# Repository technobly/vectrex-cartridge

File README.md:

Vectrex Cartridge and Vectrex LED board
===

So you wanna produce a Vectrex game and you need a 32KB cartridge with high score save support? Here's your reference design! Order it as is or customize it with your own graphics.  Supports 32KB and 64KB bankswitched games.  Supports 32KB games with DS2431+ high score save.  See Schematic for configuration options.

The RGB LED is also optional, but looks great in the translucent cartridge shells.  It lights up one of 8 colors based on the Red-Green-Blue DIP switch, yes black is a color of light ;-)

What makes this Vectrex Cartridge design different from others out there?  Well, the design is originally based on Frank Buss' Vectrex cart edge connector, but it has been significantly fixed.  The soldermask has been removed from around all of the fingers, the fingers themselves are not as wide as Frank's, and the spacing of everything has been updated to match original carts as close as possible.

Yes these fit in [Sean Kelly reproduction cartridge shells](http://www.vectrexmulti.com/order2.html#!/Vectrex-Empty-Cartridge-Shells/c/38886086/offset=0&sort=normal) perfectly!

Also included here is a simple RGB LED board add-on.  Maybe you already have a PCB but you don't have the cool LED? Easy, just add this one to the bottom.  It fits perfectly under most 28 pin 32KB/64KB EPROMS.

Got a Custom PCB logo request?
===
Join the [VEXTREME Discord server](https://discord.gg/VDssGVJ) to chat with @technobly about your request

BOM and Parts ordering
===

All the parts are described in [Bill of Materials](bom/)

You can use these Digi-Key shared carts to order the parts!
[Vectrex Cartridge](https://www.digikey.com/short/z2vf9n) or
[Vectrex LED](https://www.digikey.com/short/z2vf4d)

Ordering PCB's
===

OSHPark is a good place to order with purple or the new "after dark" theme color scheme.  You can upload the KiCad `vextrex-cartridge-tall.kicad_pcb` or `vextrex-cartridge-short.kicad_pcb` there directly.  I would download this entire Github repo ZIP file first though instead of just trying to save the PCB file from your browser.  Here's a shared link for [Vectrex LED v1.0](https://oshpark.com/shared_projects/dIH6AJOJ)

Another way to order PCB's is by using the included [gerbers-tall-design](gerbers/vectrex-cartridge-tall-v1.2.zip) or [gerbers-short-design](gerbers/vectrex-cartridge-short-v1.4.zip) and uploading those with all of the necessary specs to companies like [PCBWay](https://www.pcbway.com) or [JLCPCB](https://jlcpcb.com)

## :pencil: **Don't forget to make your board finish at least ENIG (gold flash) with a 45 degree chamfered edge. [Check out my test video here on why you don't want to settle for HASL finish.](https://www.youtube.com/watch?v=6tANHqar0rI&ab_channel=PlayVectrex)**

## :boom: **[How to Build a Vectrex Game Cartridge](https://www.youtube.com/watch?v=CAzmB-9mdWY)**

Or with hard gold contacts if you really want to spend some money, and make a cart that will last forever.

LICENSE
===

CERN OHL v2.0 Permissive - essentially do whatever you want, but if you make a ton of money off of this... [buy me some coffees please!](https://buymeacoffee.com/XzUGYrhL3)  Full [LICENSE here](LICENSE)

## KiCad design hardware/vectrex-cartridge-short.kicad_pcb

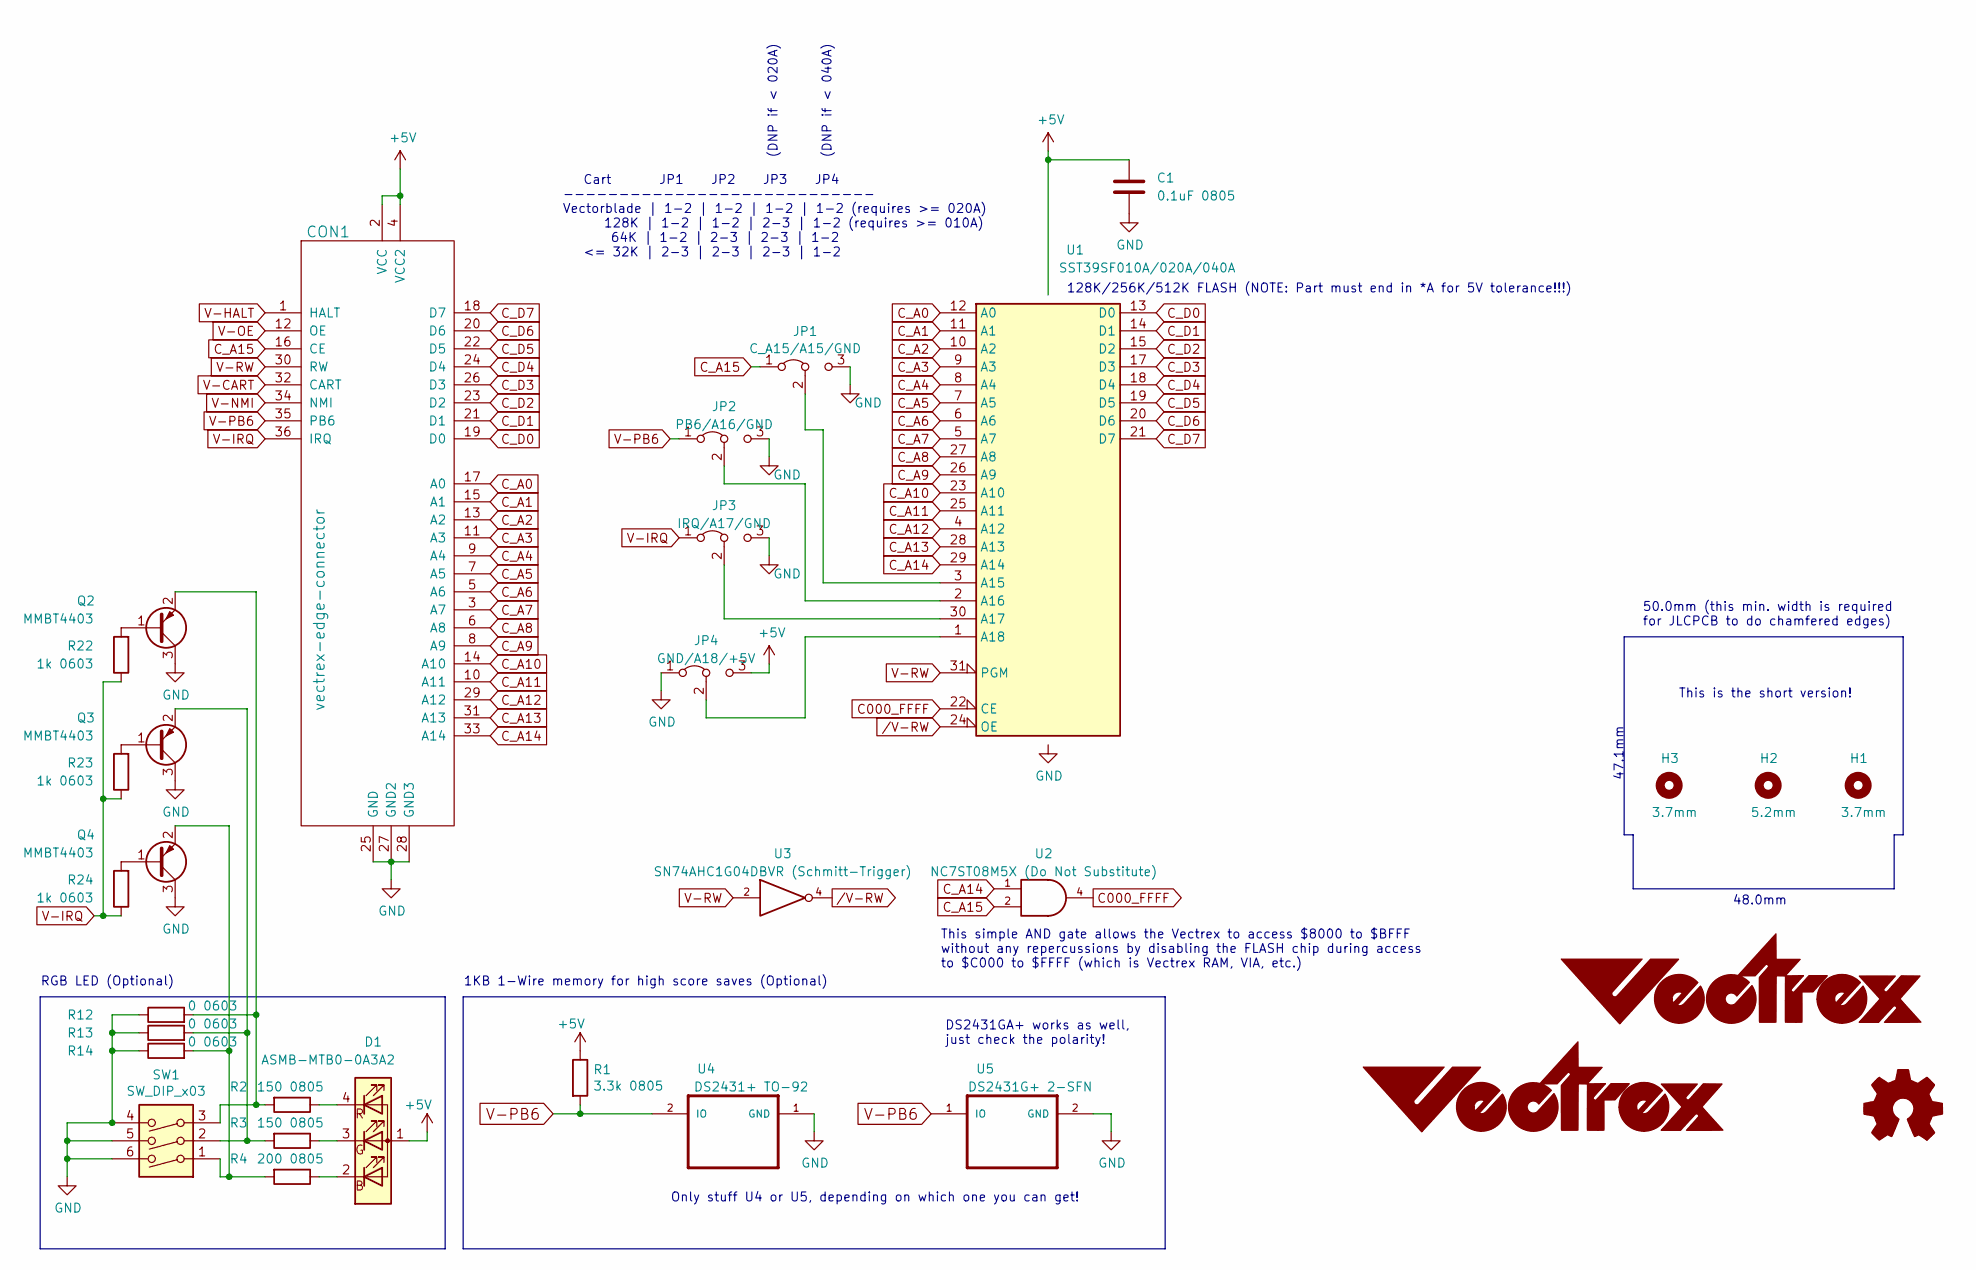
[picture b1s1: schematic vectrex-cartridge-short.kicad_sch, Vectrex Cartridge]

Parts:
C1: 0.1uF 0805; C_0805_2012Metric_Pad1.15x1.40mm_HandSolder
CON1: vectrex-edge-connector; vectrex-edge-connector-thinner-no-soldermask-no-silk
D1: ASMB-MTB0-0A3A2; LED_Avago_PLCC4_3.2x2.8mm_CW
G1: LOGO; vectrex-us-soldermask-15mm
G2: LOGO; vectrex-us-silkscreen-15mm
H1, H3: 3.7mm; Mounting_Hole_D3.7mm
H2: 5.2mm; Mounting_Hole_D5.2mm
JP1: C_A15/A15/GND; R_0603_1608Metric_Jumper_12_Bridged
JP2: PB6/A16/GND; R_0603_1608Metric_Jumper_12_Bridged
JP3: IRQ/A17/GND; R_0603_1608Metric_Jumper_12_Bridged
JP4: GND/A18/+5V; R_0603_1608Metric_Jumper_12_Bridged
Q2, Q3, Q4: MMBT4403; SOT-23
R1: 3.3k 0805; R_0805_2012Metric_Pad1.15x1.40mm_HandSolder
R2, R3: 150 0805; R_0805_2012Metric_Pad1.15x1.40mm_HandSolder
R4: 200 0805; R_0805_2012Metric_Pad1.15x1.40mm_HandSolder
R12, R13, R14: 0 0603; R_0603_1608Metric_Pad0.98x0.95mm_HandSolder
R22, R23, R24: 1k 0603; R_0603_1608Metric_Pad0.98x0.95mm_HandSolder
SW1: SW_DIP_x03; SW_DIP_SPSTx03_Slide_6.7x9.18mm_W8.61mm_P2.54mm_LowProfile_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
U1: SST39SF010A/020A/040A; PLCC-32_11.4x14.0mm_P1.27mm
U2: NC7ST08M5X (Do Not Substitute); SOT-23-5_HandSoldering
U3: SN74AHC1G04DBVR (Schmitt-Trigger); SOT-23-5_HandSoldering
U4: DS2431+ TO-92; TO-92_Inline_BW_SMT
U5: DS2431G+ 2-SFN; 2SFN_6mmx6mm

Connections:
+5V: C1.1, CON1.2 (VCC), CON1.4 (VCC2), D1.1 (A), JP4.3 (B), R1.1, U1.32 (VCC), U2.5 (VCC), U3.5 (VCC)
C000_FFFF: U1.22 (CE), U2.4
C_A0: CON1.17 (A0), U1.12 (A0)
C_A1: CON1.15 (A1), U1.11 (A1)
C_A2: CON1.13 (A2), U1.10 (A2)
C_A3: CON1.11 (A3), U1.9 (A3)
C_A4: CON1.9 (A4), U1.8 (A4)
C_A5: CON1.7 (A5), U1.7 (A5)
C_A6: CON1.5 (A6), U1.6 (A6)
C_A7: CON1.3 (A7), U1.5 (A7)
C_A8: CON1.6 (A8), U1.27 (A8)
C_A9: CON1.8 (A9), U1.26 (A9)
C_A10: CON1.14 (A10), U1.23 (A10)
C_A11: CON1.10 (A11), U1.25 (A11)
C_A12: CON1.29 (A12), U1.4 (A12)
C_A13: CON1.31 (A13), U1.28 (A13)
C_A14: CON1.33 (A14), U1.29 (A14), U2.1
C_A15: CON1.16 (CE), JP1.1 (A), U2.2
C_D0: CON1.19 (D0), U1.13 (D0)
C_D1: CON1.21 (D1), U1.14 (D1)
C_D2: CON1.23 (D2), U1.15 (D2)
C_D3: CON1.26 (D3), U1.17 (D3)
C_D4: CON1.24 (D4), U1.18 (D4)
C_D5: CON1.22 (D5), U1.19 (D5)
C_D6: CON1.20 (D6), U1.20 (D6)
C_D7: CON1.18 (D7), U1.21 (D7)
GND: C1.2, CON1.25 (GND), CON1.27 (GND2), CON1.28 (GND3), JP1.3 (B), JP2.3 (B), JP3.3 (B), JP4.1 (A), Q2.3 (C), Q3.3 (C), Q4.3 (C), R12.1, R13.1, R14.1, SW1.4, SW1.5, SW1.6, U1.16 (GND), U2.3 (GND), U3.3 (GND), U4.1 (GND), U5.2 (GND)
unnamed: D1.2 (BK), R4.1
unnamed: D1.3 (GK), R3.1
unnamed: D1.4 (RK), R2.1
unnamed: JP1.2 (C), U1.3 (A15)
unnamed: JP2.2 (C), U1.2 (A16)
unnamed: JP3.2 (C), U1.30 (A17)
unnamed: JP4.2 (C), U1.1 (A18)
unnamed: Q2.1 (B), R22.2
unnamed: Q2.2 (E), R2.2, R12.2, SW1.3
unnamed: Q3.1 (B), R23.2
unnamed: Q3.2 (E), R3.2, R13.2, SW1.2
unnamed: Q4.1 (B), R24.2
unnamed: Q4.2 (E), R4.2, R14.2, SW1.1
V-CART: CON1.32 (CART)
V-HALT: CON1.1 (HALT)
V-IRQ: CON1.36 (IRQ), JP3.1 (A), R22.1, R23.1, R24.1
V-NMI: CON1.34 (NMI)
V-OE: CON1.12 (OE)
V-PB6: CON1.35 (PB6), JP2.1 (A), R1.2, U4.2 (IO), U5.1 (IO)
V-RW: CON1.30 (RW), U1.31 (PGM), U3.2
/V-RW: U1.24 (OE), U3.4

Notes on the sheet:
Only stuff U4 or U5, depending on which one you can get!
50.0mm (this min. width is required for JLCPCB to do chamfered edges)
(DNP if < 020A)
1KB 1-Wire memory for high score saves (Optional)
RGB LED (Optional)
48.0mm
This is the short version!
Cart JP1 JP2 JP3 JP4 ---------------------------- Vectorblade | 1-2 | 1-2 | 1-2 | 1-2 (requires >= 020A) 128K | 1-2 | 1-2 | 2-3 | 1-2 (requires >= 010A) 64K | 1-2 | 2-3 | 2-3 | 1-2 <= 32K | 2-3 | 2-3 | 2-3 | 1-2
128K/256K/512K FLASH (NOTE: Part must end in *A for 5V tolerance!!!)
DS2431GA+ works as well, just check the polarity!
(DNP if < 040A)
47.1mm
This simple AND gate allows the Vectrex to access $8000 to $BFFF without any repercussions by disabling the FLASH chip during access to $C000 to $FFFF (which is Vectrex RAM, VIA, etc.)

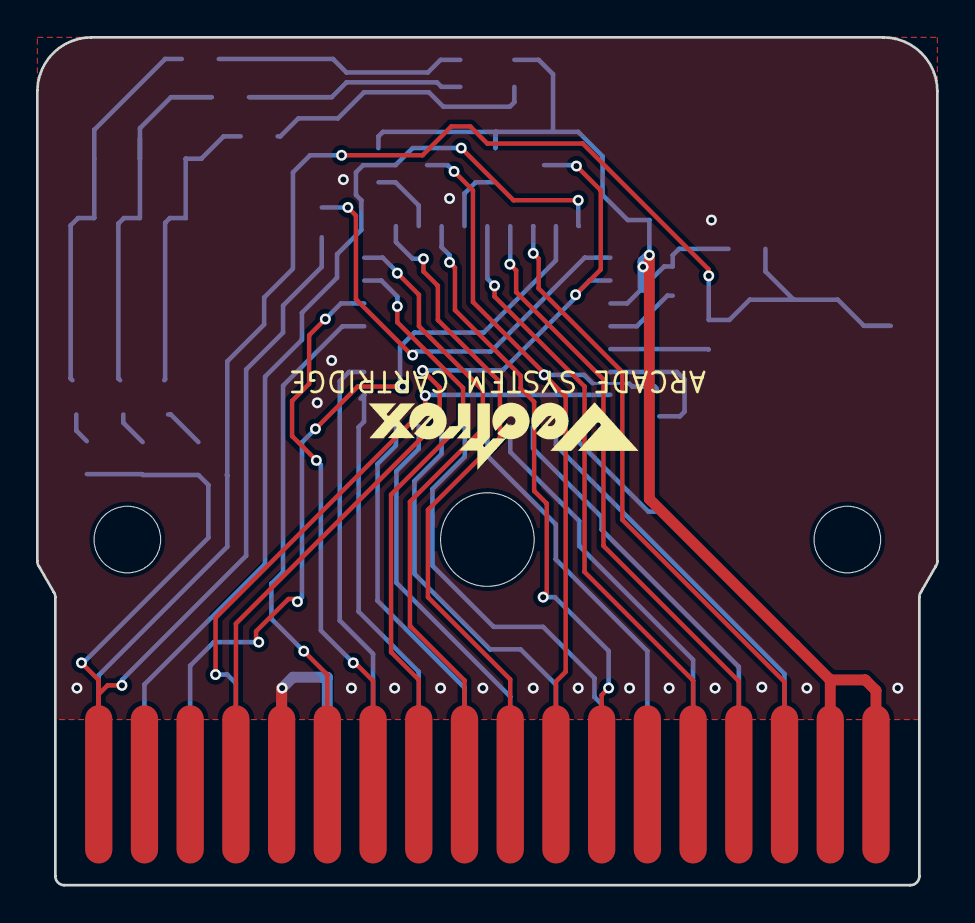
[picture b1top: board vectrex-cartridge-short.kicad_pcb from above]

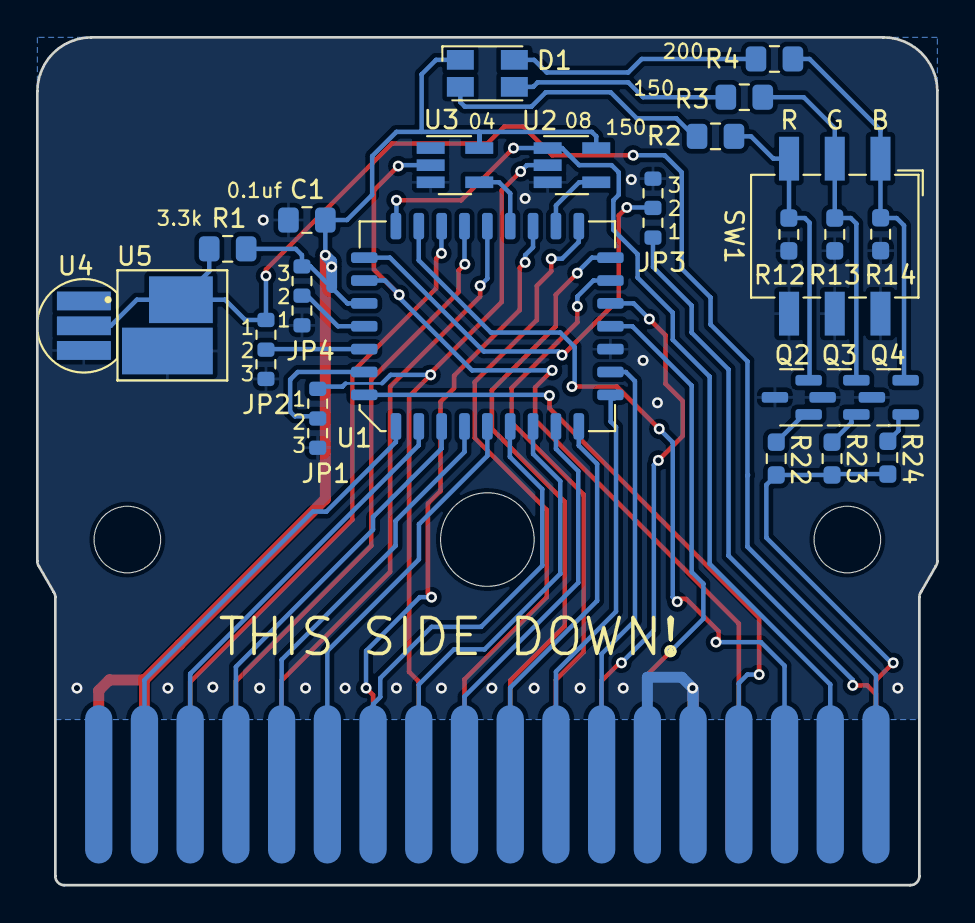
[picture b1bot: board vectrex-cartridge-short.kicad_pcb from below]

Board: 2 copper layers, 50.0 x 47.1 mm, 31 parts (26 on the bottom side), 44 nets.

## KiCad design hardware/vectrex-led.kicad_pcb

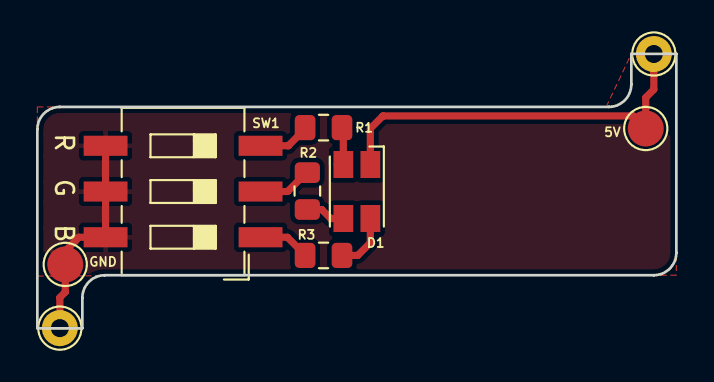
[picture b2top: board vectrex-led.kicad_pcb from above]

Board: 2 copper layers, 35.5 x 15.2 mm, 10 parts (0 on the bottom side), 8 nets.

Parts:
D1: ASMB-MTB0-0A3A2; LED_Avago_PLCC4_3.2x2.8mm_CW
G1: LOGO; vectrex-us-soldermask-15mm
H1, H2: MountingHole_Pad; TestPoint_THTPad_D2.0mm_Drill1.0mm
R1, R2: 220 0805; R_0805_2012Metric_Pad1.15x1.40mm_HandSolder
R3: 150 0805; R_0805_2012Metric_Pad1.15x1.40mm_HandSolder
SW1: SW_DIP_x03; SW_DIP_SPSTx03_Slide_6.7x9.18mm_W8.61mm_P2.54mm_LowProfile
TP1, TP2: TestPoint; TestPoint_Pad_D2.0mm

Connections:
+5V: D1.1, H1.1, TP1.1
GND: H2.1, SW1.4, SW1.5, SW1.6, TP2.1
unnamed: D1.2, R3.1
unnamed: D1.3, R2.1
unnamed: D1.4, R1.1
unnamed: R1.2, SW1.3
unnamed: R2.2, SW1.2
unnamed: R3.2, SW1.1

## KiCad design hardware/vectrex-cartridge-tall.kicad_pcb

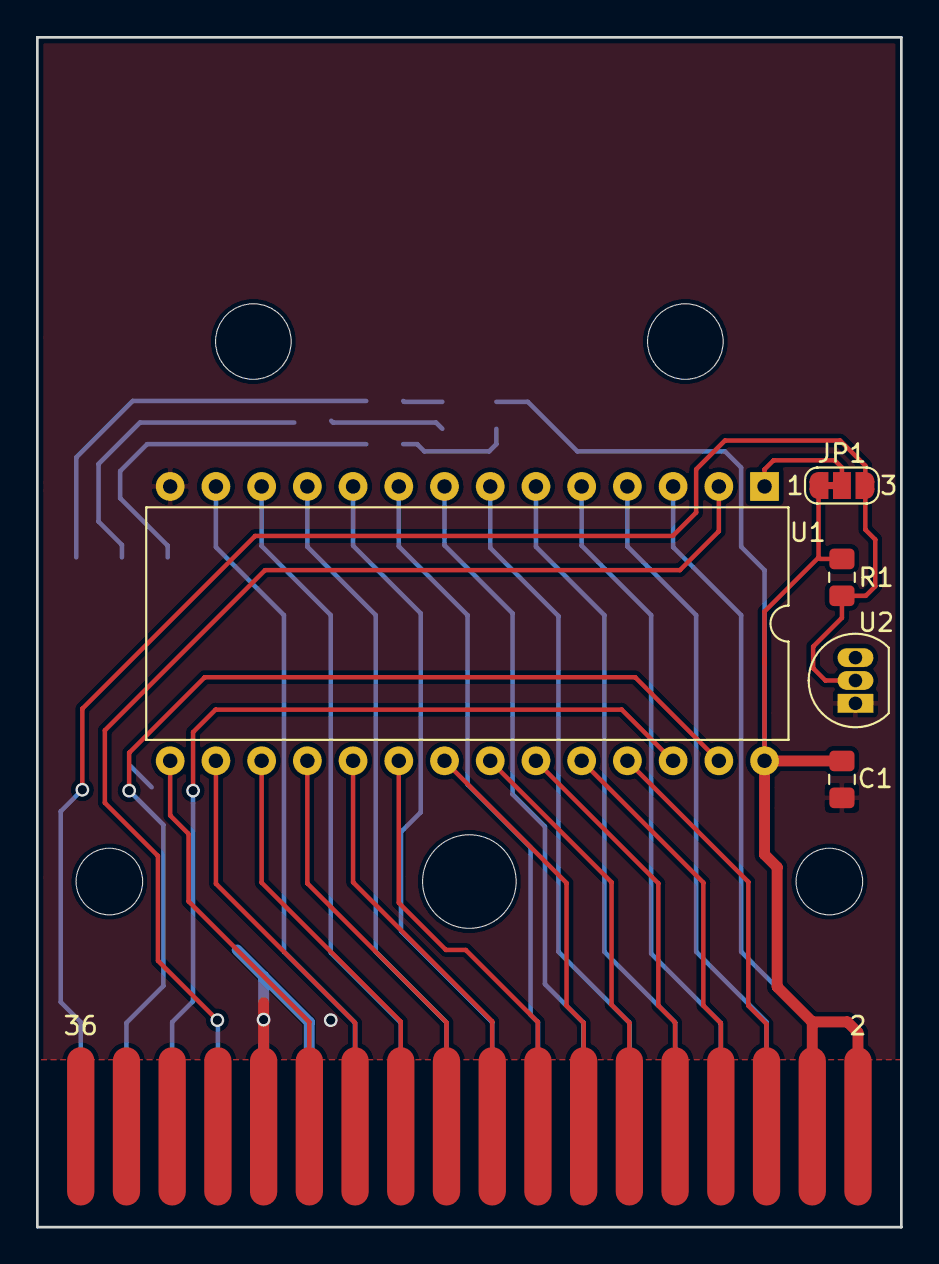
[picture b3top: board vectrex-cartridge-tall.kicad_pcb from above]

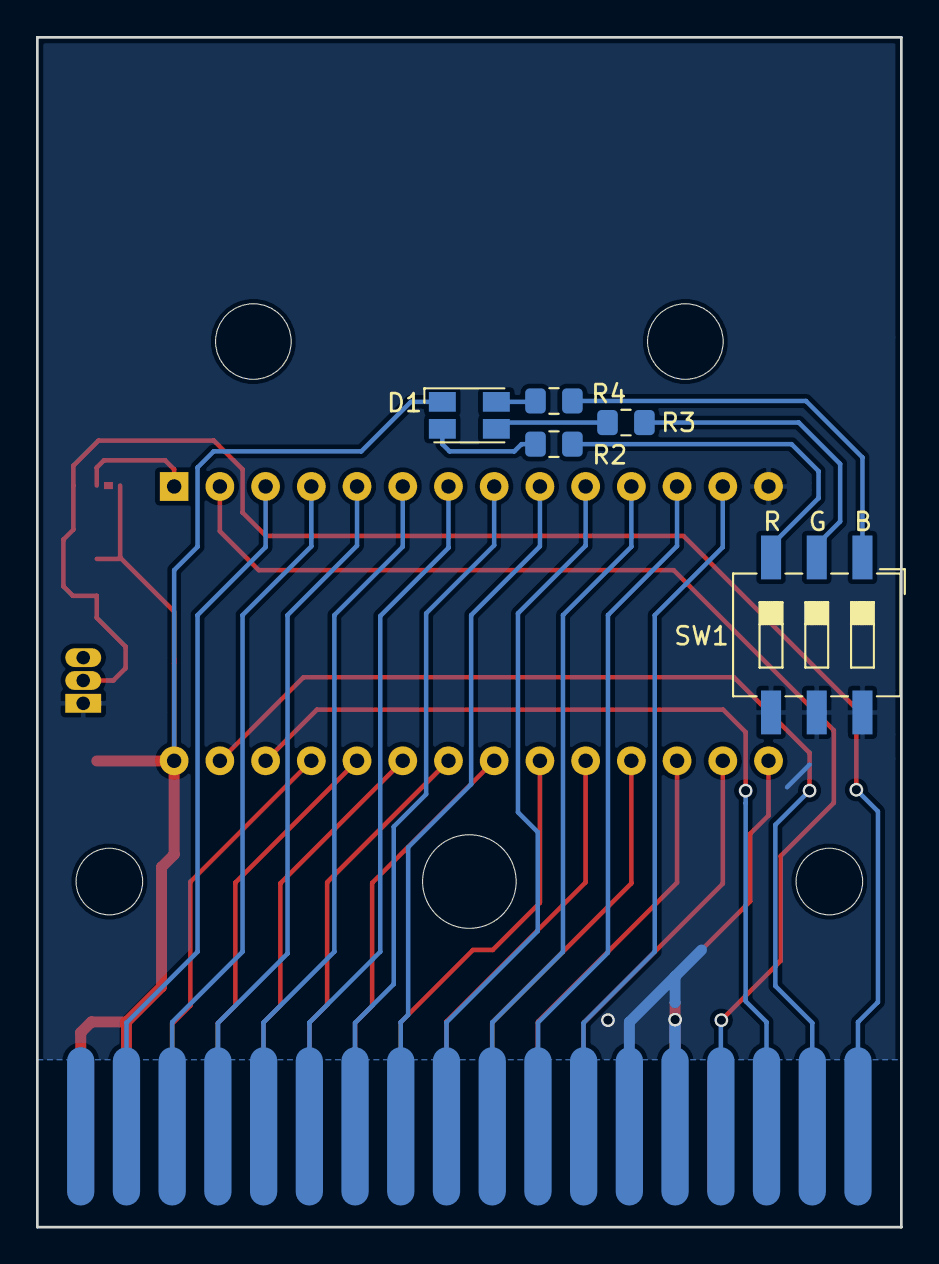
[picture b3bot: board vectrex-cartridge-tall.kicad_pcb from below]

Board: 2 copper layers, 48.0 x 66.1 mm, 18 parts (6 on the bottom side), 35 nets.

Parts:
C1: 0.1uF 0805; C_0805_2012Metric_Pad1.15x1.40mm_HandSolder
CON1: vectrex-edge-connector; vectrex-edge-connector-thinner-no-soldermask
D1: ASMB-MTB0-0A3A2; LED_Avago_PLCC4_3.2x2.8mm_CW
G1: LOGO; vectrex-us-soldermask
G3: LOGO; vectrex-uk-soldermask
H1, H3: 3.7mm; Mounting_Hole_D3.7mm
H2: 5.2mm; Mounting_Hole_D5.2mm
H4, H5: 4.2mm; Mounting_Hole_D4.2mm
JP1: SolderJumper_3_Bridged12; SolderJumper-3_P1.3mm_Bridged12_RoundedPad1.0x1.5mm_NumberL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
R1: 3.3k 0805; R_0805_2012Metric_Pad1.15x1.40mm_HandSolder
R2, R3: 200 0805; R_0805_2012Metric_Pad1.15x1.40mm_HandSolder
R4: 120 0805; R_0805_2012Metric_Pad1.15x1.40mm_HandSolder
SW1: SW_DIP_x03; SW_DIP_SPSTx03_Slide_6.7x9.18mm_W8.61mm_P2.54mm_LowProfile
U1: AT27C256R-70PU / AT27C512R-70PU; DIP-28_W15.24mm
U2: DS2431+ TO-92; TO-92_Inline_BW

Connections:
+5V: C1.1, CON1.2, CON1.4, D1.1, JP1.1, R1.1, U1.28
C_A0: CON1.17, U1.10
C_A1: CON1.15, U1.9
C_A2: CON1.13, U1.8
C_A3: CON1.11, U1.7
C_A4: CON1.9, U1.6
C_A5: CON1.7, U1.5
C_A6: CON1.5, U1.4
C_A7: CON1.3, U1.3
C_A8: CON1.6, U1.25
C_A9: CON1.8, U1.24
C_A10: CON1.14, U1.21
C_A11: CON1.10, U1.23
C_A12: CON1.29, U1.2
C_A13: CON1.31, U1.26
C_A14: CON1.33, U1.27
C_D0: CON1.19, U1.11
C_D1: CON1.21, U1.12
C_D2: CON1.23, U1.13
C_D3: CON1.26, U1.15
C_D4: CON1.24, U1.16
C_D5: CON1.22, U1.17
C_D6: CON1.20, U1.18
C_D7: CON1.18, U1.19
GND: C1.2, CON1.25, CON1.27, CON1.28, SW1.4, SW1.5, SW1.6, U1.14, U2.1
unnamed: D1.2, R4.1
unnamed: D1.3, R3.1
unnamed: D1.4, R2.1
unnamed: JP1.2, U1.1
unnamed: R2.2, SW1.3
unnamed: R3.2, SW1.2
unnamed: R4.2, SW1.1
V-CE: CON1.16, U1.20
V-OE: CON1.12, U1.22
V-PB6: CON1.35, JP1.3, R1.2, U2.2

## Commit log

2020-06-21 initial release v1.0
2020-06-22 added short design gerber zip file
2020-06-29 added RGB LED to Vectrex Cartridge v1.1, also added stand-alone LED PCB v1.0
2020-06-29 added example glow in a clear shell
2020-07-05 Updated DS2431 footprint, and many little tweaks for v1.2
2020-09-25 Updated LED resistor values for deeper colors.
2022-11-29 migrate symbol libraries to KiCad 6.x
2022-11-29 migrate 3D shapes to built-in KiCad 6.x location
2022-11-29 update RGB LED resistor values for deeper color
2024-01-14 update vectrex-cartridge-short to v1.4 all SMT
2026-03-23 Fix README
